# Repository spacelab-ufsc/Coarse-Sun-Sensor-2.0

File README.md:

# Coarse-Sun-Sensor-2.0
Fine Sun Sensor unit to be implemented as a subsystem in the team's first ADCS

Some of the features:
- Low surface area;
- Low cost;
- 4 small area photodiodes (cross pattern);
- 2 grounded (M2 bolt) fixation points;
- 5 terminal Picoblade external connection;
- I2C external interface;
- Photovoltaic mode (zero-bias) TIA amplifier for hardware dark current minimization;

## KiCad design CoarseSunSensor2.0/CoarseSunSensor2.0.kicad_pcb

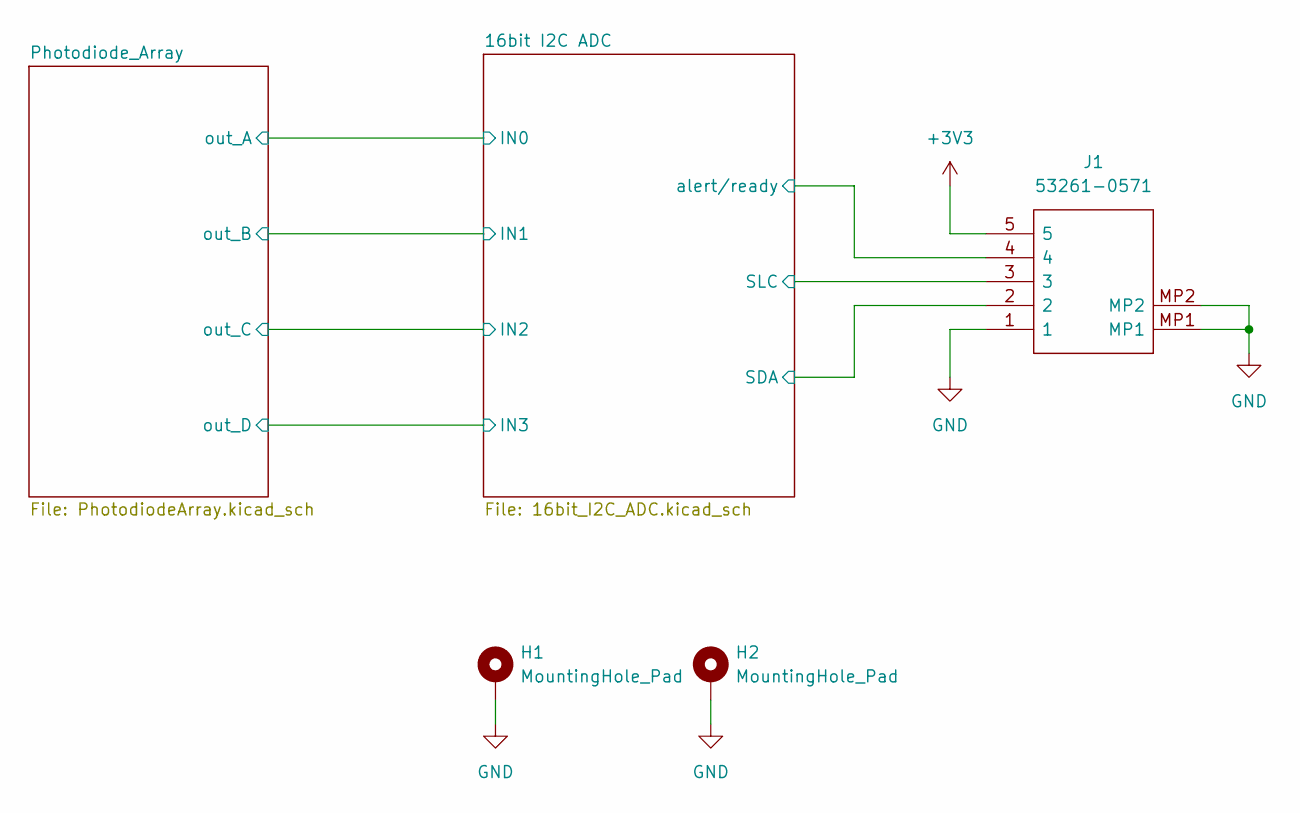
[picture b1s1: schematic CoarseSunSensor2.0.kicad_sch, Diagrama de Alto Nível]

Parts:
H1, H2: MountingHole_Pad; MountingHole_2.2mm_M2_ISO7380_Pad_TopOnly
J1: 53261-0571; 532610571TR250; Mouser Part Number 538-53261-0571

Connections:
+3V3: J1.5; also elsewhere on the board
/16bit I2C ADC/SDA: J1.2; also elsewhere on the board
/16bit I2C ADC/SLC: J1.3; also elsewhere on the board
/16bit I2C ADC/alert/ready: J1.4; also elsewhere on the board
GND: H1.1, H2.1, J1.1, J1.MP1, J1.MP2; also elsewhere on the board

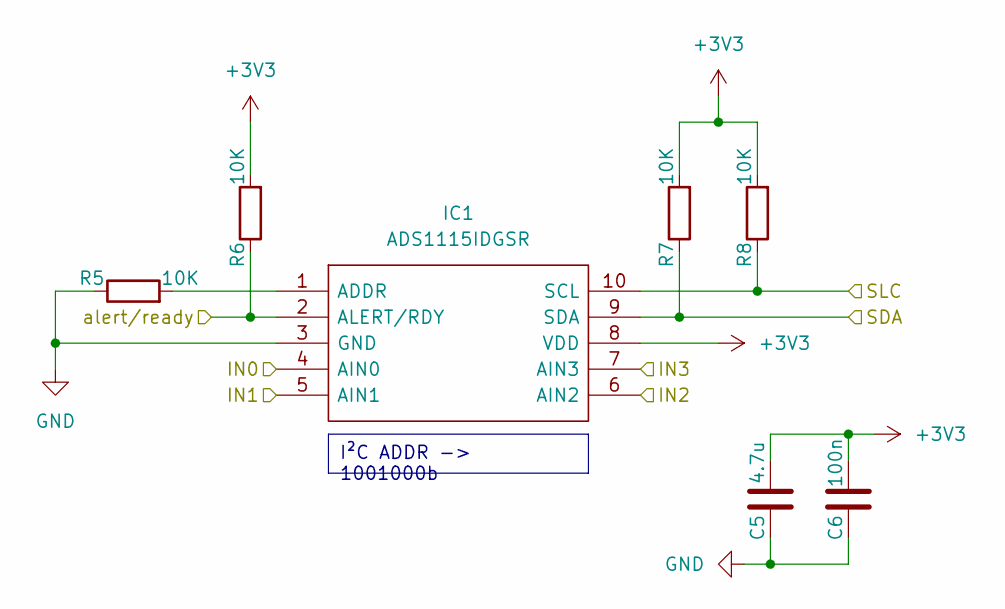
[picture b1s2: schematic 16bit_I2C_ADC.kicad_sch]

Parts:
C5: 4.7u; C_0603_1608Metric
C6: 100n; C_0603_1608Metric
IC1: ADS1115IDGSR; SOP50P490X110-10N; Mouser Part Number 595-ADS1115IDGSR
R5, R6, R7, R8: 10K; R_0603_1608Metric

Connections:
+3V3: C5.2, C6.2, IC1.8 (VDD), R6.2, R7.2, R8.2; also elsewhere on the board
/16bit I2C ADC/IN0: IC1.4 (AIN0); also elsewhere on the board
/16bit I2C ADC/IN1: IC1.5 (AIN1); also elsewhere on the board
/16bit I2C ADC/IN2: IC1.6 (AIN2); also elsewhere on the board
/16bit I2C ADC/IN3: IC1.7 (AIN3); also elsewhere on the board
/16bit I2C ADC/SDA: IC1.9 (SDA), R7.1; also elsewhere on the board
/16bit I2C ADC/SLC: IC1.10 (SCL), R8.1; also elsewhere on the board
/16bit I2C ADC/alert/ready: IC1.2 (ALERT/RDY), R6.1; also elsewhere on the board
GND: C5.1, C6.1, IC1.3 (GND), R5.1; also elsewhere on the board
unnamed: IC1.1 (ADDR), R5.2

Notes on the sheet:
I²C ADDR -> 1001000b

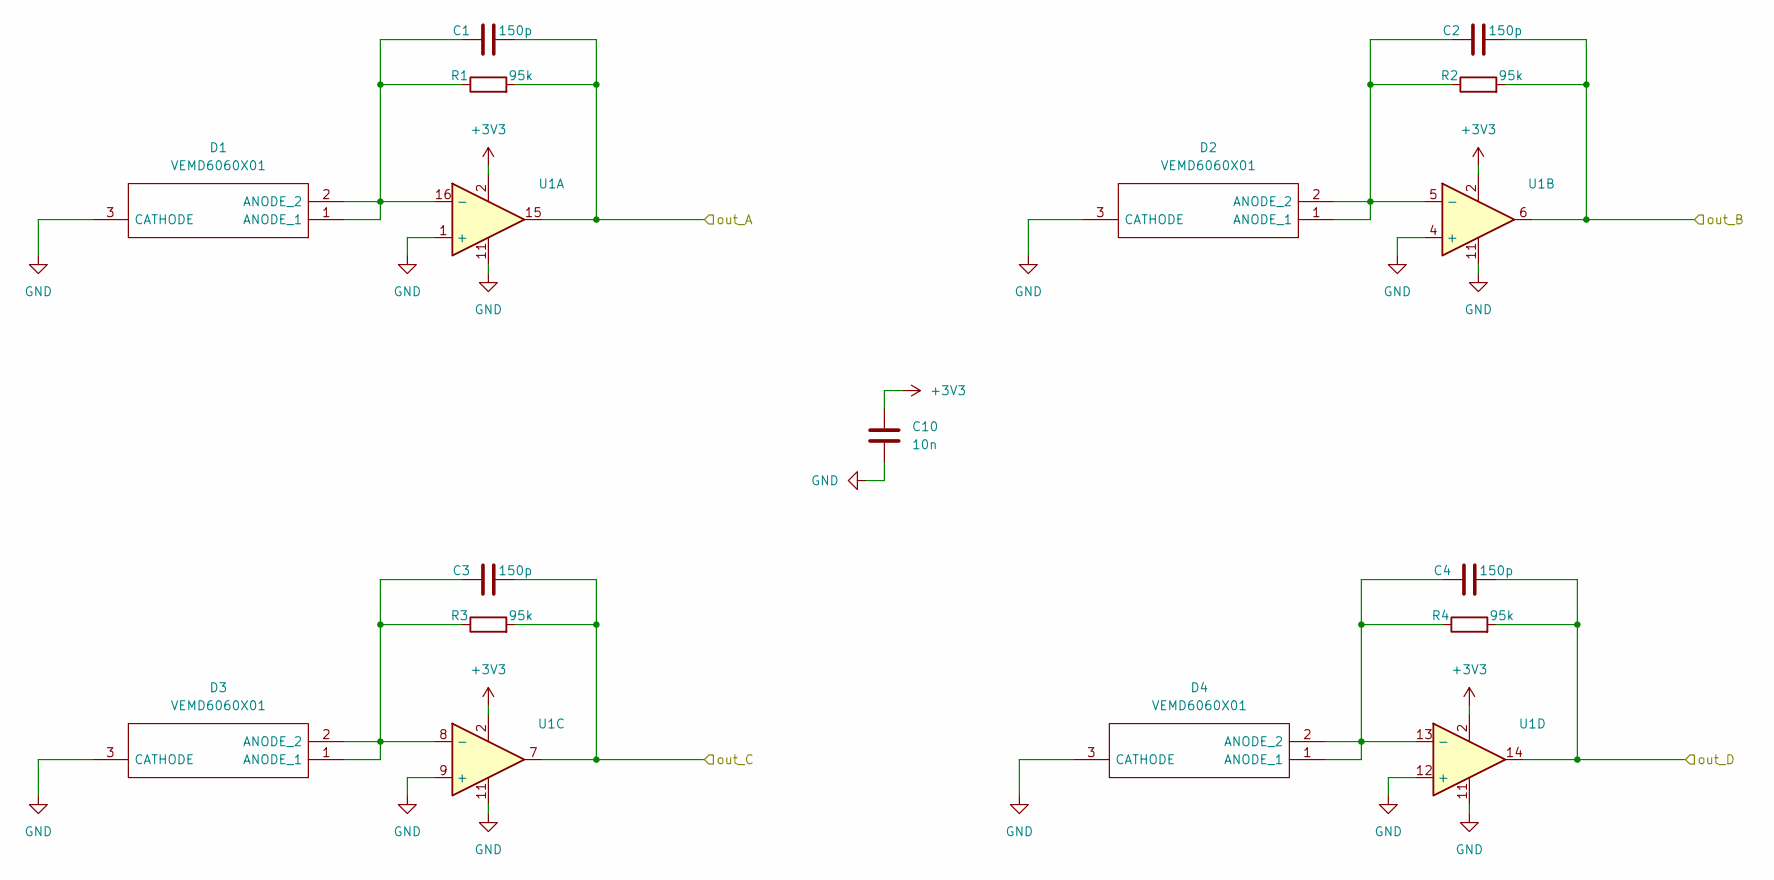
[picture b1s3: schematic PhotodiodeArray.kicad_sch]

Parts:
C1, C2, C3, C4: 150p; C_0603_1608Metric
C10: 10n; C_0603_1608Metric
D1, D2, D3, D4: VEMD6060X01; Mouser Part Number 78-VEMD6060X01
R1, R2, R3, R4: 95k; R_0603_1608Metric
U1: QFN50P300X300X100-17N

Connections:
+3V3: C10.1, U1.2; also elsewhere on the board
/16bit I2C ADC/IN0: C1.2, R1.2, U1.15; also elsewhere on the board
/16bit I2C ADC/IN1: C2.2, R2.2, U1.6; also elsewhere on the board
/16bit I2C ADC/IN2: C3.2, R3.2, U1.7; also elsewhere on the board
/16bit I2C ADC/IN3: C4.2, R4.2, U1.14; also elsewhere on the board
GND: C10.2, D1.3 (CATHODE), D2.3 (CATHODE), D3.3 (CATHODE), D4.3 (CATHODE), U1.1 (+), U1.4 (+), U1.9 (+), U1.11, U1.12 (+); also elsewhere on the board
unnamed: C1.1, D1.1 (ANODE_1), D1.2 (ANODE_2), R1.1, U1.16 (-)
unnamed: C2.1, D2.1 (ANODE_1), D2.2 (ANODE_2), R2.1, U1.5 (-)
unnamed: C3.1, D3.1 (ANODE_1), D3.2 (ANODE_2), R3.1, U1.8 (-)
unnamed: C4.1, D4.1 (ANODE_1), D4.2 (ANODE_2), R4.1, U1.13 (-)

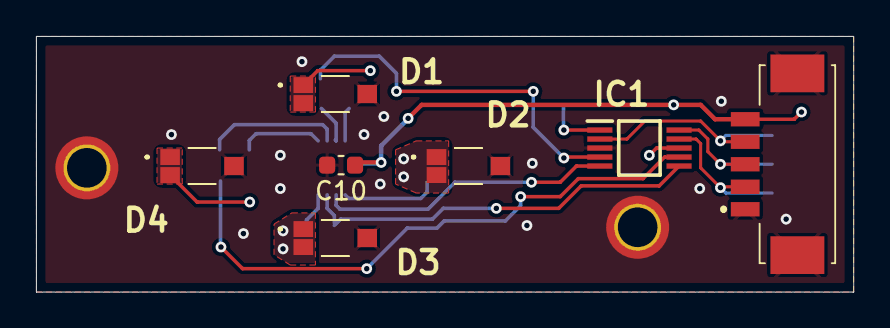
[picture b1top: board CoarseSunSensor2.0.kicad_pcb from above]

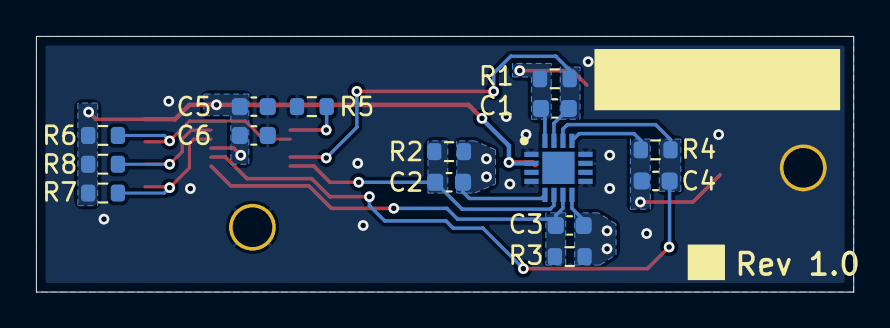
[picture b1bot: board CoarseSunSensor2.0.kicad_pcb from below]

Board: 2 copper layers, 45.4 x 14.2 mm, 24 parts (15 on the bottom side), 14 nets.

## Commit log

2025-06-07 Major changes
    fiz tudo
2025-06-07 Board repositioning
2025-06-12 Minor schematic changes
    Calculei o valor dos capacitores e resistores
2025-06-12 DRC exclusions
